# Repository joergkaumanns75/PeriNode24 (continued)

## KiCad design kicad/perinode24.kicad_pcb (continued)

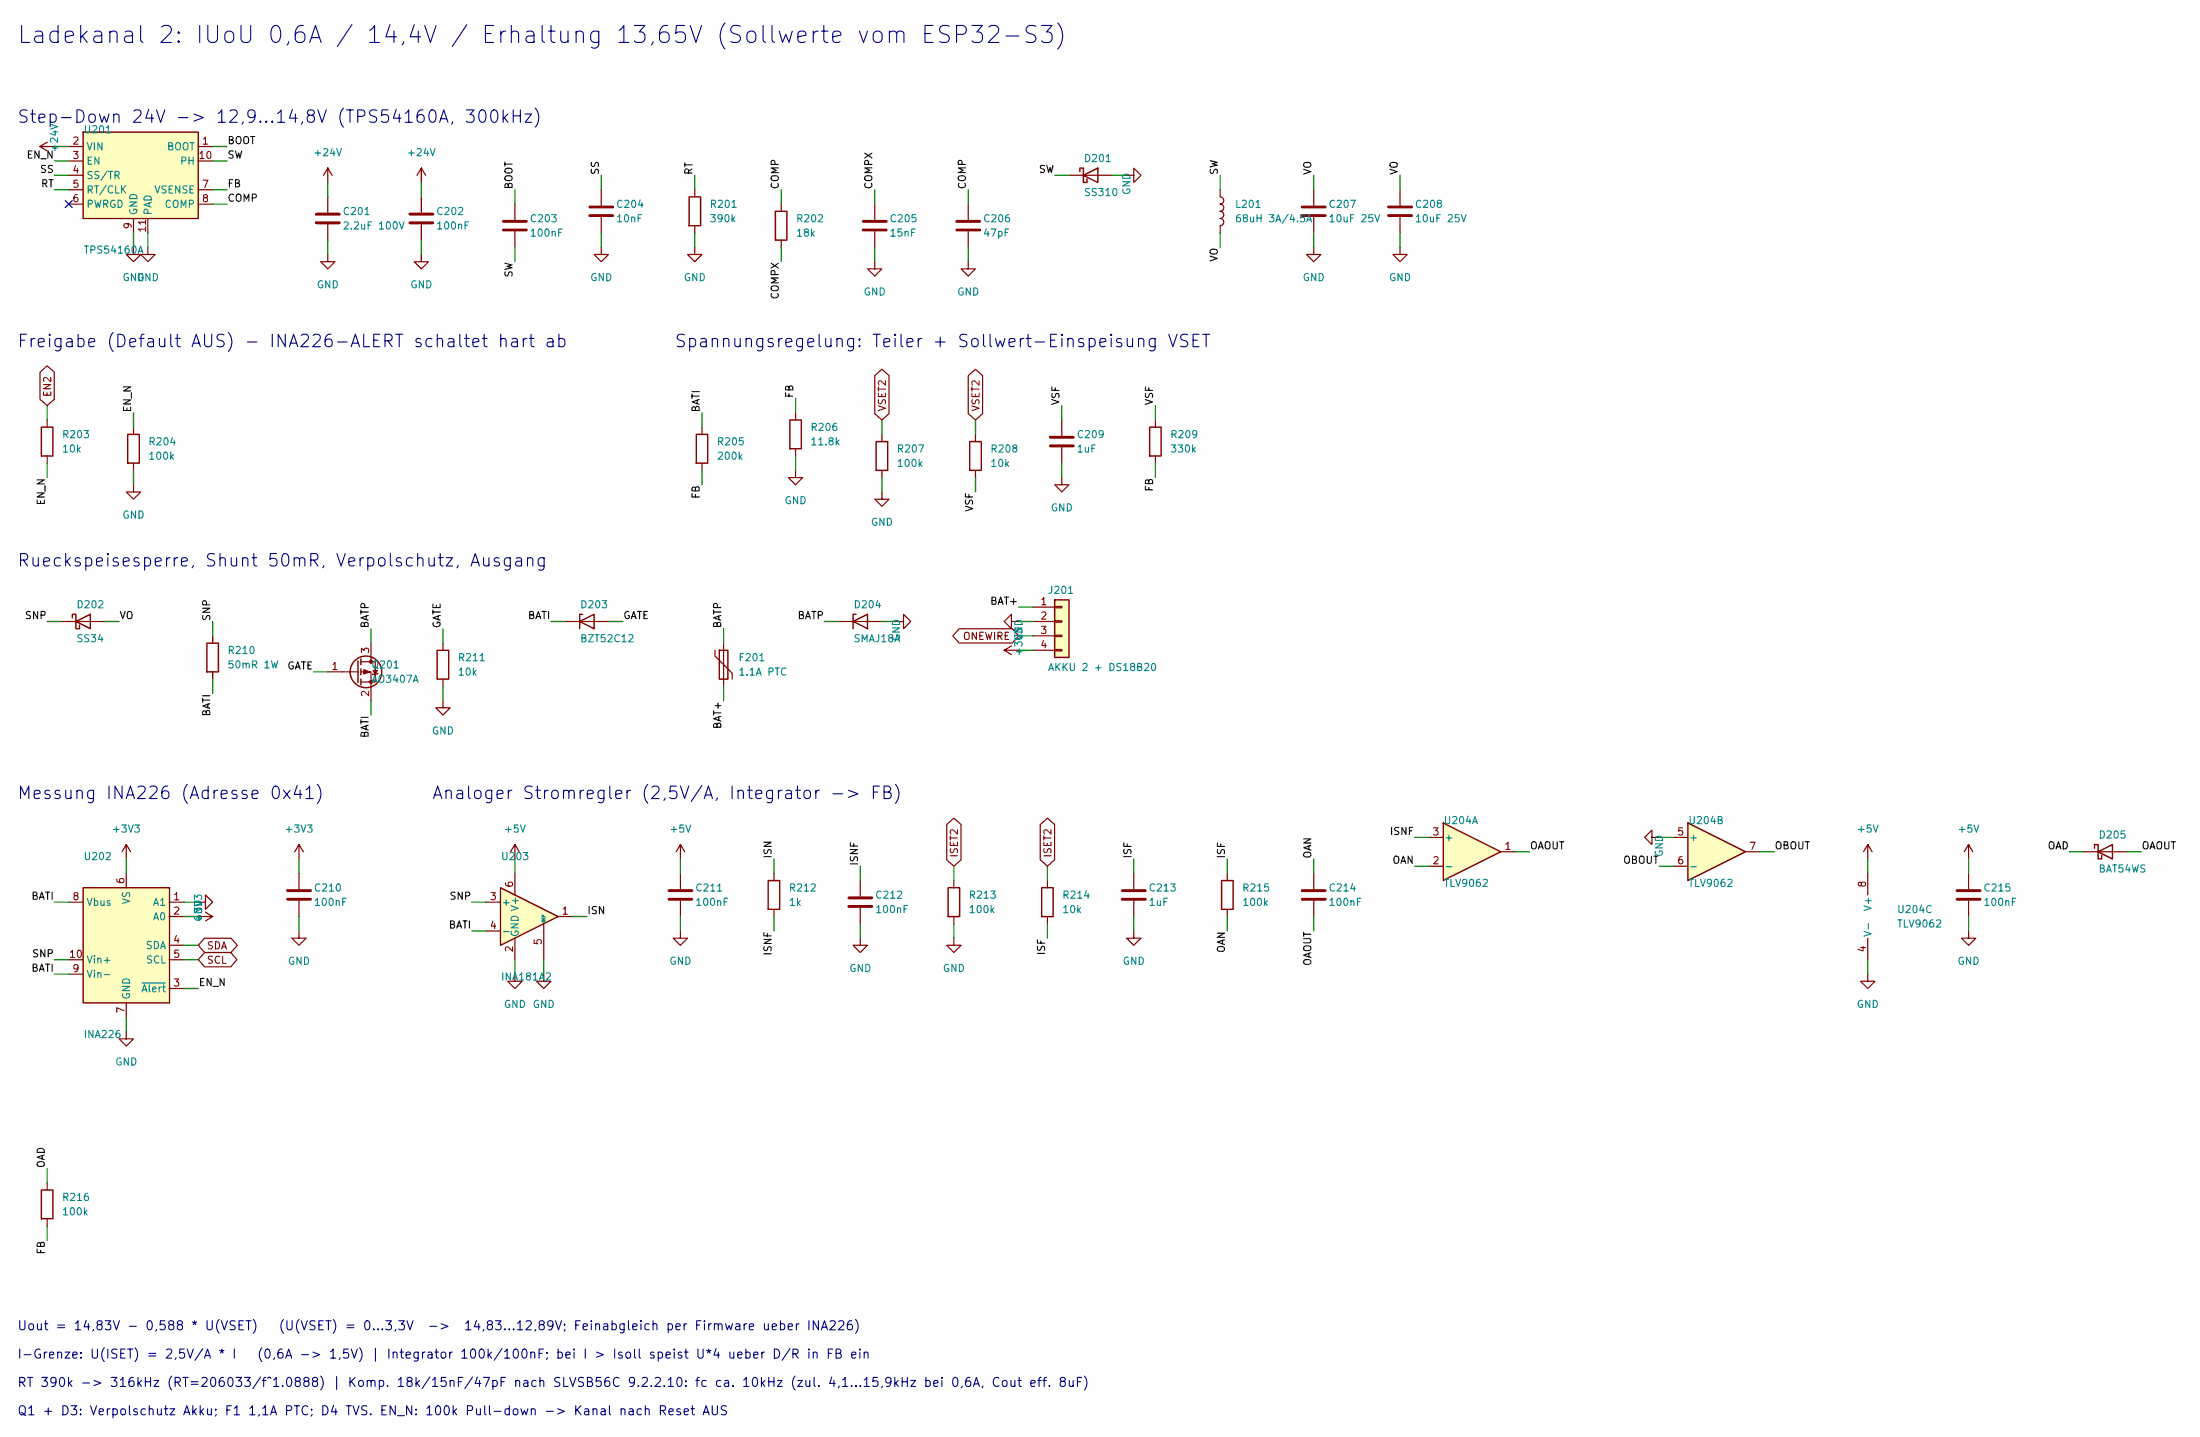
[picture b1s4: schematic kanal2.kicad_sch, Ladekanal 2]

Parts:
C201: 2.2uF 100V; C_1210_3225Metric; MPN CL32B225KCJSNNE; LCSC C55151
C202, C203, C210, C211, C212, C214, C215: 100nF; C_0603_1608Metric; MPN CC0603KRX7R9BB104; LCSC C14663
C204: 10nF; C_0603_1608Metric; MPN 0603B103K500NT; LCSC C57112
C205: 15nF; C_0603_1608Metric; MPN 0603B153K500CT; LCSC C296018
C206: 47pF; C_0603_1608Metric; MPN 0603CG470J500NT; LCSC C1671
C207, C208: 10uF 25V; C_0805_2012Metric; MPN CL21A106KAYNNNE; LCSC C15850
C209, C213: 1uF; C_0603_1608Metric; MPN CL10A105KB8NNNC; LCSC C15849
D201: SS310; D_SMA; MPN SS310; LCSC C15874
D202: SS34; D_SMA; MPN SS34; LCSC C8678
D203: BZT52C12; D_SOD-123; MPN BZT52C12; LCSC C2891780
D204: SMAJ18A; D_SMA; MPN SMAJ18A; LCSC C148219
D205: BAT54WS; D_SOD-323; MPN BAT54WS; LCSC C3040452
F201: 1.1A PTC; Fuse_1812_4532Metric; MPN 1812L110/16DR; LCSC C142746
J201: AKKU 2 + DS18B20; JST_PH_S4B-PH-SM4-TB_1x04-1MP_P2.00mm_Horizontal; MPN S4B-PH-SM4-TB(LF)(SN); LCSC C265102
L201: 68uH 3A/4.5A; L_TaiTech_TMPC1265_13.5x12.5mm; MPN FXL1360-680-M; LCSC C526032
Q201: AO3407A; SOT-23; MPN AO3407A; LCSC C15155
R201: 390k; R_0603_1608Metric; MPN 0603WAF3903T5E; LCSC C23150
R202: 18k; R_0603_1608Metric; MPN 0603WAF1802T5E; LCSC C25810
R203, R208, R211, R214: 10k; R_0603_1608Metric; MPN 0603WAF1002T5E; LCSC C25804
R204, R207, R213, R215, R216: 100k; R_0603_1608Metric; MPN 0603WAF1003T5E; LCSC C25803
R205: 200k; R_0603_1608Metric; MPN 0603WAF2003T5E; LCSC C25811
R206: 11.8k; R_0603_1608Metric; MPN RMC060311.8K1%N; LCSC C325665
R209: 330k; R_0603_1608Metric; MPN 0603WAF3303T5E; LCSC C23137
R210: 50mR 1W; R_1206_3216Metric; MPN RLM12FTCMR050; LCSC C912768
R212: 1k; R_0603_1608Metric; MPN 0603WAF1001T5E; LCSC C21190
U201: TPS54160A; MSOP-10-1EP_3x3mm_P0.5mm_EP1.68x1.88mm_ThermalVias; MPN TPS54160ADGQR; LCSC C390949
U202: INA226; VSSOP-10_3x3mm_P0.5mm; MPN INA226AIDGSR; LCSC C49851
U203: INA181A2; SOT-23-6; MPN INA181A2IDBVR; LCSC C2058784
U204: TLV9062; SOIC-8_3.9x4.9mm_P1.27mm; MPN TLV9062IDR; LCSC C398355

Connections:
+3V3: C210.1, J201.4, U202.2 (A0), U202.6 (VS); also elsewhere on the board
+5V: C211.1, C215.1, U203.6 (V+), U204.8 (V+); also elsewhere on the board
+24V: C201.1, C202.1, U201.2 (VIN); also elsewhere on the board
/Ladekanal 2/BAT+: F201.2, J201.1
/Ladekanal 2/BATI: D203.1 (K), Q201.2 (S), R205.1, R210.2, U202.8 (Vbus), U202.9 (Vin-), U203.4 (-)
/Ladekanal 2/BATP: D204.1 (K), F201.1, Q201.3 (D)
/Ladekanal 2/BOOT: C203.1, U201.1 (BOOT)
/Ladekanal 2/COMP: C206.1, R202.1, U201.8 (COMP)
/Ladekanal 2/COMPX: C205.1, R202.2
/Ladekanal 2/EN_N: R203.2, R204.1, U201.3 (EN), U202.3 (~Alert)
/Ladekanal 2/FB: R205.2, R206.1, R209.2, R216.2, U201.7 (VSENSE)
/Ladekanal 2/GATE: D203.2 (A), Q201.1 (G), R211.1
/Ladekanal 2/ISF: C213.1, R214.2, R215.1
/Ladekanal 2/ISN: R212.1, U203.1
/Ladekanal 2/ISNF: C212.1, R212.2, U204.3 (+)
/Ladekanal 2/OAD: D205.1 (K), R216.1
/Ladekanal 2/OAN: C214.1, R215.2, U204.2 (-)
/Ladekanal 2/OAOUT: C214.2, D205.2 (A), U204.1
/Ladekanal 2/OBOUT: U204.6 (-), U204.7
/Ladekanal 2/RT: R201.1, U201.5 (RT/CLK)
/Ladekanal 2/SNP: D202.1 (K), R210.1, U202.10 (Vin+), U203.3 (+)
/Ladekanal 2/SS: C204.1, U201.4 (SS/TR)
/Ladekanal 2/SW: C203.2, D201.1 (K), L201.1, U201.10 (PH)
/Ladekanal 2/VO: C207.1, C208.1, D202.2 (A), L201.2
/Ladekanal 2/VSF: C209.1, R208.2, R209.1
EN2: R203.1; also elsewhere on the board
GND: C201.2, C202.2, C204.2, C205.2, C206.2, C207.2, C208.2, C209.2, C210.2, C211.2, C212.2, C213.2, C215.2, D201.2 (A), D204.2 (A), J201.2, R201.2, R204.2, R206.2, R207.2, R211.2, R213.2, U201.9 (GND), U201.11 (PAD), U202.1 (A1), U202.7 (GND), U203.2 (GND), U203.5 (REF), U204.4 (V-), U204.5 (+); also elsewhere on the board
ISET2: R213.1, R214.1; also elsewhere on the board
ONEWIRE: J201.3; also elsewhere on the board
SCL: U202.5 (SCL); also elsewhere on the board
SDA: U202.4 (SDA); also elsewhere on the board
VSET2: R207.1, R208.1; also elsewhere on the board

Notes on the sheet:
I-Grenze: U(ISET) = 2,5V/A * I (0,6A -> 1,5V) | Integrator 100k/100nF; bei I > Isoll speist U*4 ueber D/R in FB ein
Step-Down 24V -> 12,9...14,8V (TPS54160A, 300kHz)
Uout = 14,83V - 0,588 * U(VSET) (U(VSET) = 0...3,3V -> 14,83...12,89V; Feinabgleich per Firmware ueber INA226)
Analoger Stromregler (2,5V/A, Integrator -> FB)
Freigabe (Default AUS) - INA226-ALERT schaltet hart ab
Rueckspeisesperre, Shunt 50mR, Verpolschutz, Ausgang
Spannungsregelung: Teiler + Sollwert-Einspeisung VSET
Q1 + D3: Verpolschutz Akku; F1 1,1A PTC; D4 TVS. EN_N: 100k Pull-down -> Kanal nach Reset AUS
Messung INA226 (Adresse 0x41)
RT 390k -> 316kHz (RT=206033/f^1.0888) | Komp. 18k/15nF/47pF nach SLVSB56C 9.2.2.10: fc ca. 10kHz (zul. 4,1...15,9kHz bei 0,6A, Cout eff. 8uF)
Ladekanal 2: IUoU 0,6A / 14,4V / Erhaltung 13,65V (Sollwerte vom ESP32-S3)

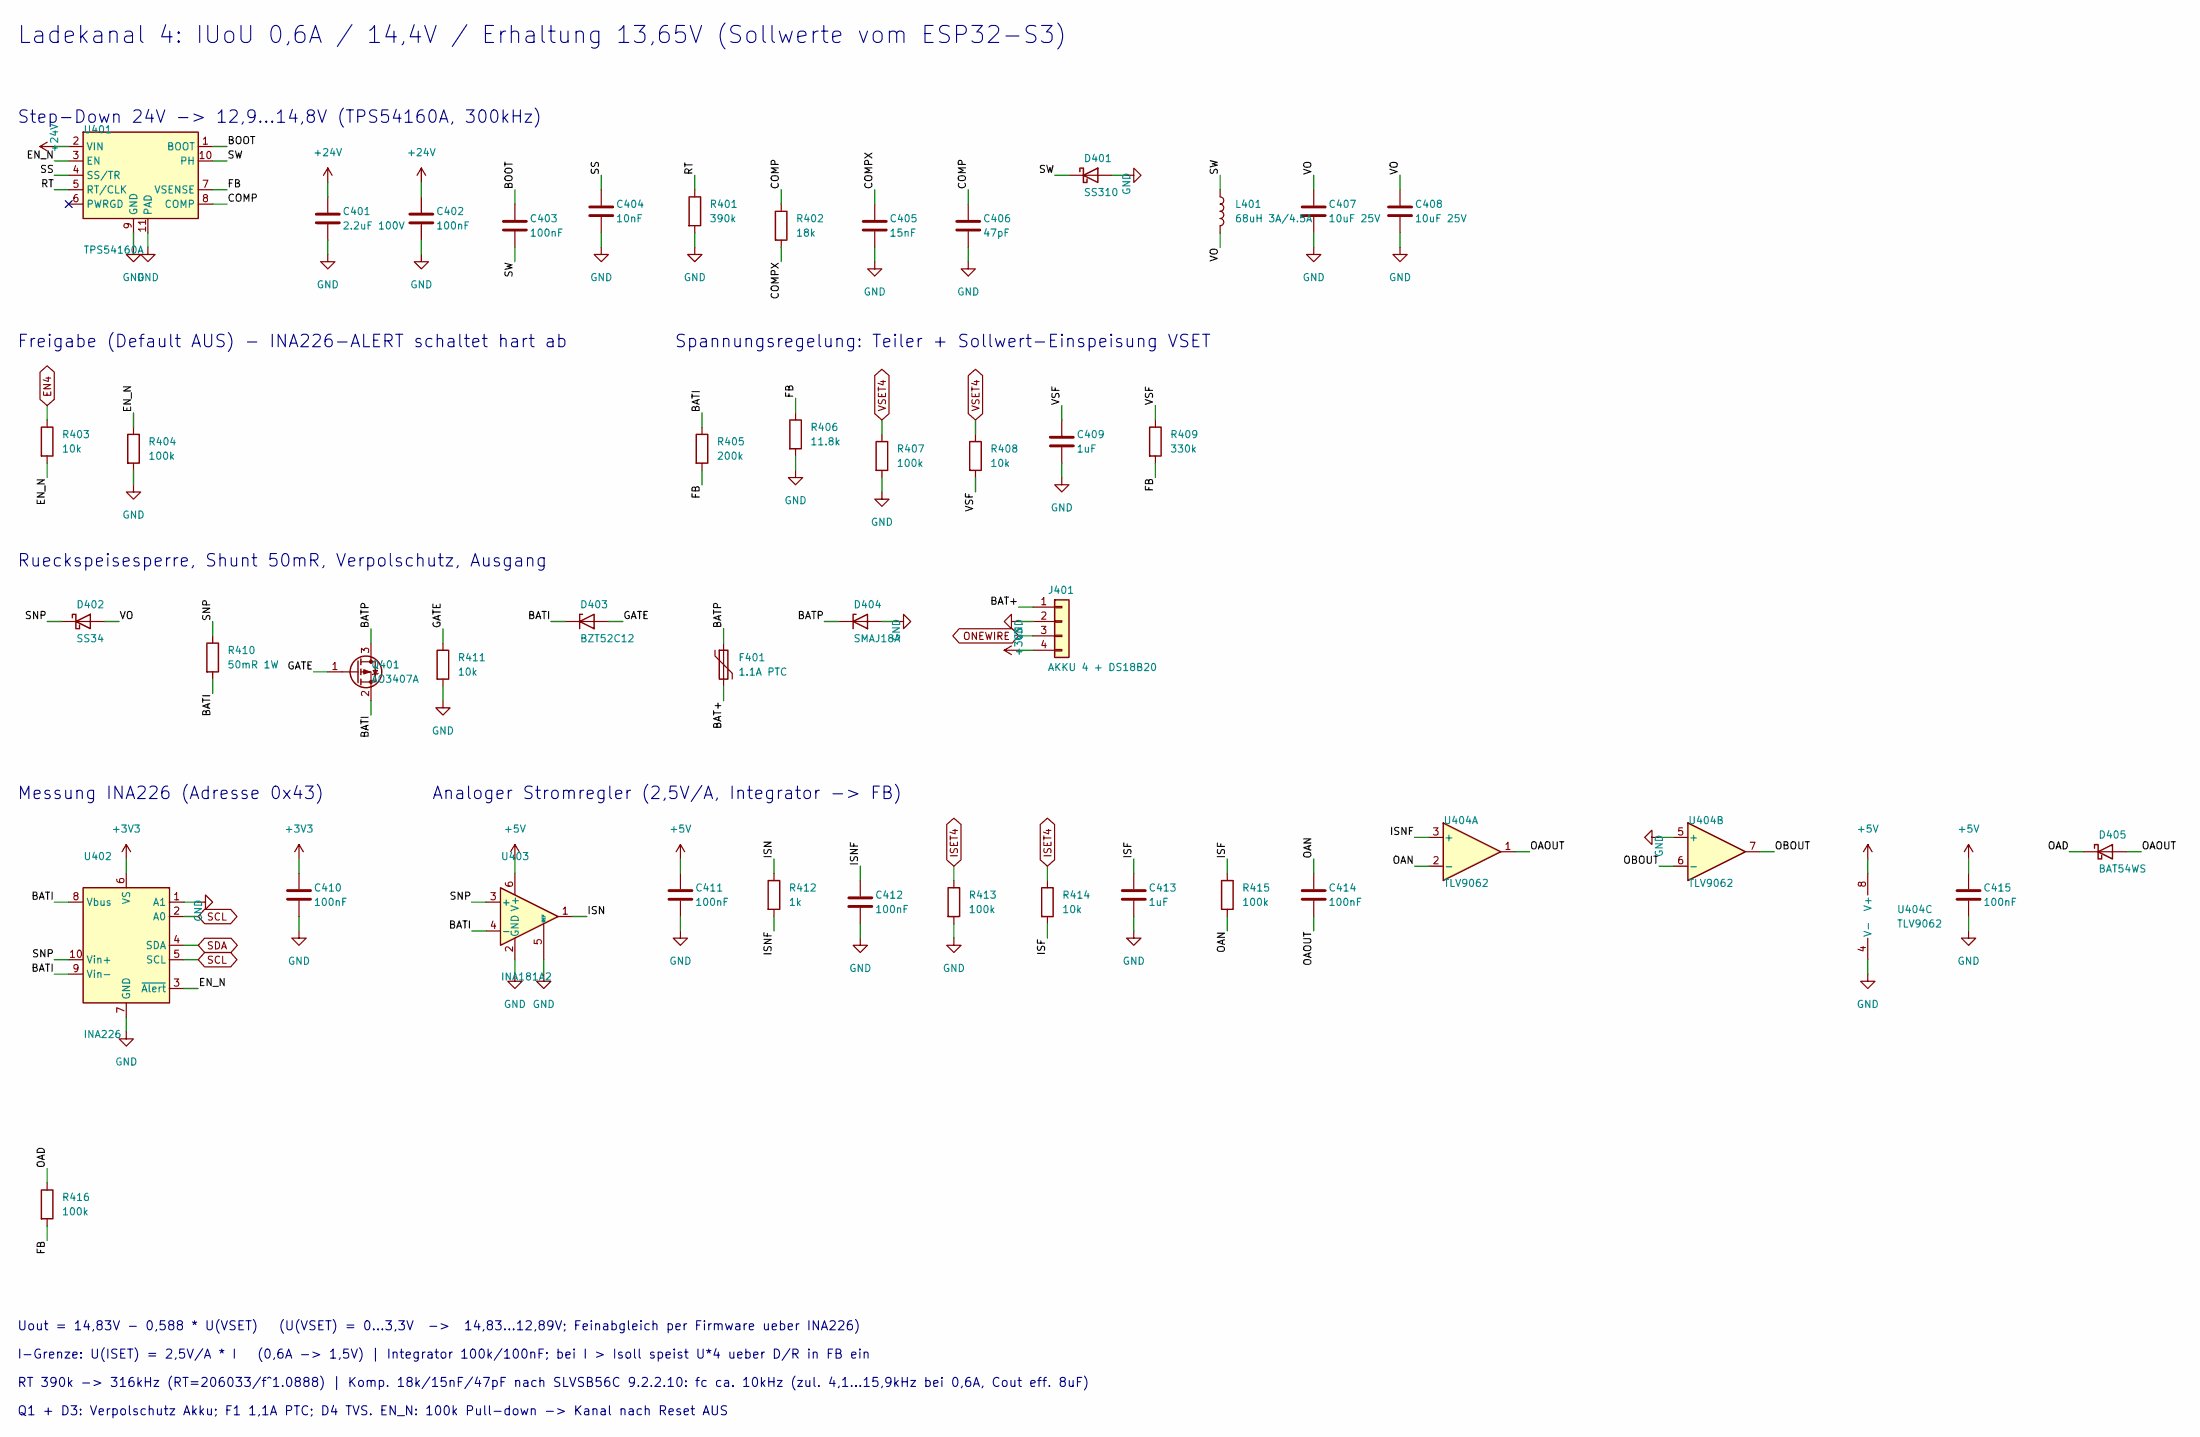
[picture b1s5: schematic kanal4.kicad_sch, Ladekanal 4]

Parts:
C401: 2.2uF 100V; C_1210_3225Metric; MPN CL32B225KCJSNNE; LCSC C55151
C402, C403, C410, C411, C412, C414, C415: 100nF; C_0603_1608Metric; MPN CC0603KRX7R9BB104; LCSC C14663
C404: 10nF; C_0603_1608Metric; MPN 0603B103K500NT; LCSC C57112
C405: 15nF; C_0603_1608Metric; MPN 0603B153K500CT; LCSC C296018
C406: 47pF; C_0603_1608Metric; MPN 0603CG470J500NT; LCSC C1671
C407, C408: 10uF 25V; C_0805_2012Metric; MPN CL21A106KAYNNNE; LCSC C15850
C409, C413: 1uF; C_0603_1608Metric; MPN CL10A105KB8NNNC; LCSC C15849
D401: SS310; D_SMA; MPN SS310; LCSC C15874
D402: SS34; D_SMA; MPN SS34; LCSC C8678
D403: BZT52C12; D_SOD-123; MPN BZT52C12; LCSC C2891780
D404: SMAJ18A; D_SMA; MPN SMAJ18A; LCSC C148219
D405: BAT54WS; D_SOD-323; MPN BAT54WS; LCSC C3040452
F401: 1.1A PTC; Fuse_1812_4532Metric; MPN 1812L110/16DR; LCSC C142746
J401: AKKU 4 + DS18B20; JST_PH_S4B-PH-SM4-TB_1x04-1MP_P2.00mm_Horizontal; MPN S4B-PH-SM4-TB(LF)(SN); LCSC C265102
L401: 68uH 3A/4.5A; L_TaiTech_TMPC1265_13.5x12.5mm; MPN FXL1360-680-M; LCSC C526032
Q401: AO3407A; SOT-23; MPN AO3407A; LCSC C15155
R401: 390k; R_0603_1608Metric; MPN 0603WAF3903T5E; LCSC C23150
R402: 18k; R_0603_1608Metric; MPN 0603WAF1802T5E; LCSC C25810
R403, R408, R411, R414: 10k; R_0603_1608Metric; MPN 0603WAF1002T5E; LCSC C25804
R404, R407, R413, R415, R416: 100k; R_0603_1608Metric; MPN 0603WAF1003T5E; LCSC C25803
R405: 200k; R_0603_1608Metric; MPN 0603WAF2003T5E; LCSC C25811
R406: 11.8k; R_0603_1608Metric; MPN RMC060311.8K1%N; LCSC C325665
R409: 330k; R_0603_1608Metric; MPN 0603WAF3303T5E; LCSC C23137
R410: 50mR 1W; R_1206_3216Metric; MPN RLM12FTCMR050; LCSC C912768
R412: 1k; R_0603_1608Metric; MPN 0603WAF1001T5E; LCSC C21190
U401: TPS54160A; MSOP-10-1EP_3x3mm_P0.5mm_EP1.68x1.88mm_ThermalVias; MPN TPS54160ADGQR; LCSC C390949
U402: INA226; VSSOP-10_3x3mm_P0.5mm; MPN INA226AIDGSR; LCSC C49851
U403: INA181A2; SOT-23-6; MPN INA181A2IDBVR; LCSC C2058784
U404: TLV9062; SOIC-8_3.9x4.9mm_P1.27mm; MPN TLV9062IDR; LCSC C398355

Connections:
+3V3: C410.1, J401.4, U402.6 (VS); also elsewhere on the board
+5V: C411.1, C415.1, U403.6 (V+), U404.8 (V+); also elsewhere on the board
+24V: C401.1, C402.1, U401.2 (VIN); also elsewhere on the board
/Ladekanal 4/BAT+: F401.2, J401.1
/Ladekanal 4/BATI: D403.1 (K), Q401.2 (S), R405.1, R410.2, U402.8 (Vbus), U402.9 (Vin-), U403.4 (-)
/Ladekanal 4/BATP: D404.1 (K), F401.1, Q401.3 (D)
/Ladekanal 4/BOOT: C403.1, U401.1 (BOOT)
/Ladekanal 4/COMP: C406.1, R402.1, U401.8 (COMP)
/Ladekanal 4/COMPX: C405.1, R402.2
/Ladekanal 4/EN_N: R403.2, R404.1, U401.3 (EN), U402.3 (~Alert)
/Ladekanal 4/FB: R405.2, R406.1, R409.2, R416.2, U401.7 (VSENSE)
/Ladekanal 4/GATE: D403.2 (A), Q401.1 (G), R411.1
/Ladekanal 4/ISF: C413.1, R414.2, R415.1
/Ladekanal 4/ISN: R412.1, U403.1
/Ladekanal 4/ISNF: C412.1, R412.2, U404.3 (+)
/Ladekanal 4/OAD: D405.1 (K), R416.1
/Ladekanal 4/OAN: C414.1, R415.2, U404.2 (-)
/Ladekanal 4/OAOUT: C414.2, D405.2 (A), U404.1
/Ladekanal 4/OBOUT: U404.6 (-), U404.7
/Ladekanal 4/RT: R401.1, U401.5 (RT/CLK)
/Ladekanal 4/SNP: D402.1 (K), R410.1, U402.10 (Vin+), U403.3 (+)
/Ladekanal 4/SS: C404.1, U401.4 (SS/TR)
/Ladekanal 4/SW: C403.2, D401.1 (K), L401.1, U401.10 (PH)
/Ladekanal 4/VO: C407.1, C408.1, D402.2 (A), L401.2
/Ladekanal 4/VSF: C409.1, R408.2, R409.1
EN4: R403.1; also elsewhere on the board
GND: C401.2, C402.2, C404.2, C405.2, C406.2, C407.2, C408.2, C409.2, C410.2, C411.2, C412.2, C413.2, C415.2, D401.2 (A), D404.2 (A), J401.2, R401.2, R404.2, R406.2, R407.2, R411.2, R413.2, U401.9 (GND), U401.11 (PAD), U402.1 (A1), U402.7 (GND), U403.2 (GND), U403.5 (REF), U404.4 (V-), U404.5 (+); also elsewhere on the board
ISET4: R413.1, R414.1; also elsewhere on the board
ONEWIRE: J401.3; also elsewhere on the board
SCL: U402.2 (A0), U402.5 (SCL); also elsewhere on the board
SDA: U402.4 (SDA); also elsewhere on the board
VSET4: R407.1, R408.1; also elsewhere on the board

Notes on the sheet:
Ladekanal 4: IUoU 0,6A / 14,4V / Erhaltung 13,65V (Sollwerte vom ESP32-S3)
Step-Down 24V -> 12,9...14,8V (TPS54160A, 300kHz)
Freigabe (Default AUS) - INA226-ALERT schaltet hart ab
Spannungsregelung: Teiler + Sollwert-Einspeisung VSET
Rueckspeisesperre, Shunt 50mR, Verpolschutz, Ausgang
Messung INA226 (Adresse 0x43)
Analoger Stromregler (2,5V/A, Integrator -> FB)
Uout = 14,83V - 0,588 * U(VSET) (U(VSET) = 0...3,3V -> 14,83...12,89V; Feinabgleich per Firmware ueber INA226)
I-Grenze: U(ISET) = 2,5V/A * I (0,6A -> 1,5V) | Integrator 100k/100nF; bei I > Isoll speist U*4 ueber D/R in FB ein
RT 390k -> 316kHz (RT=206033/f^1.0888) | Komp. 18k/15nF/47pF nach SLVSB56C 9.2.2.10: fc ca. 10kHz (zul. 4,1...15,9kHz bei 0,6A, Cout eff. 8uF)
Q1 + D3: Verpolschutz Akku; F1 1,1A PTC; D4 TVS. EN_N: 100k Pull-down -> Kanal nach Reset AUS

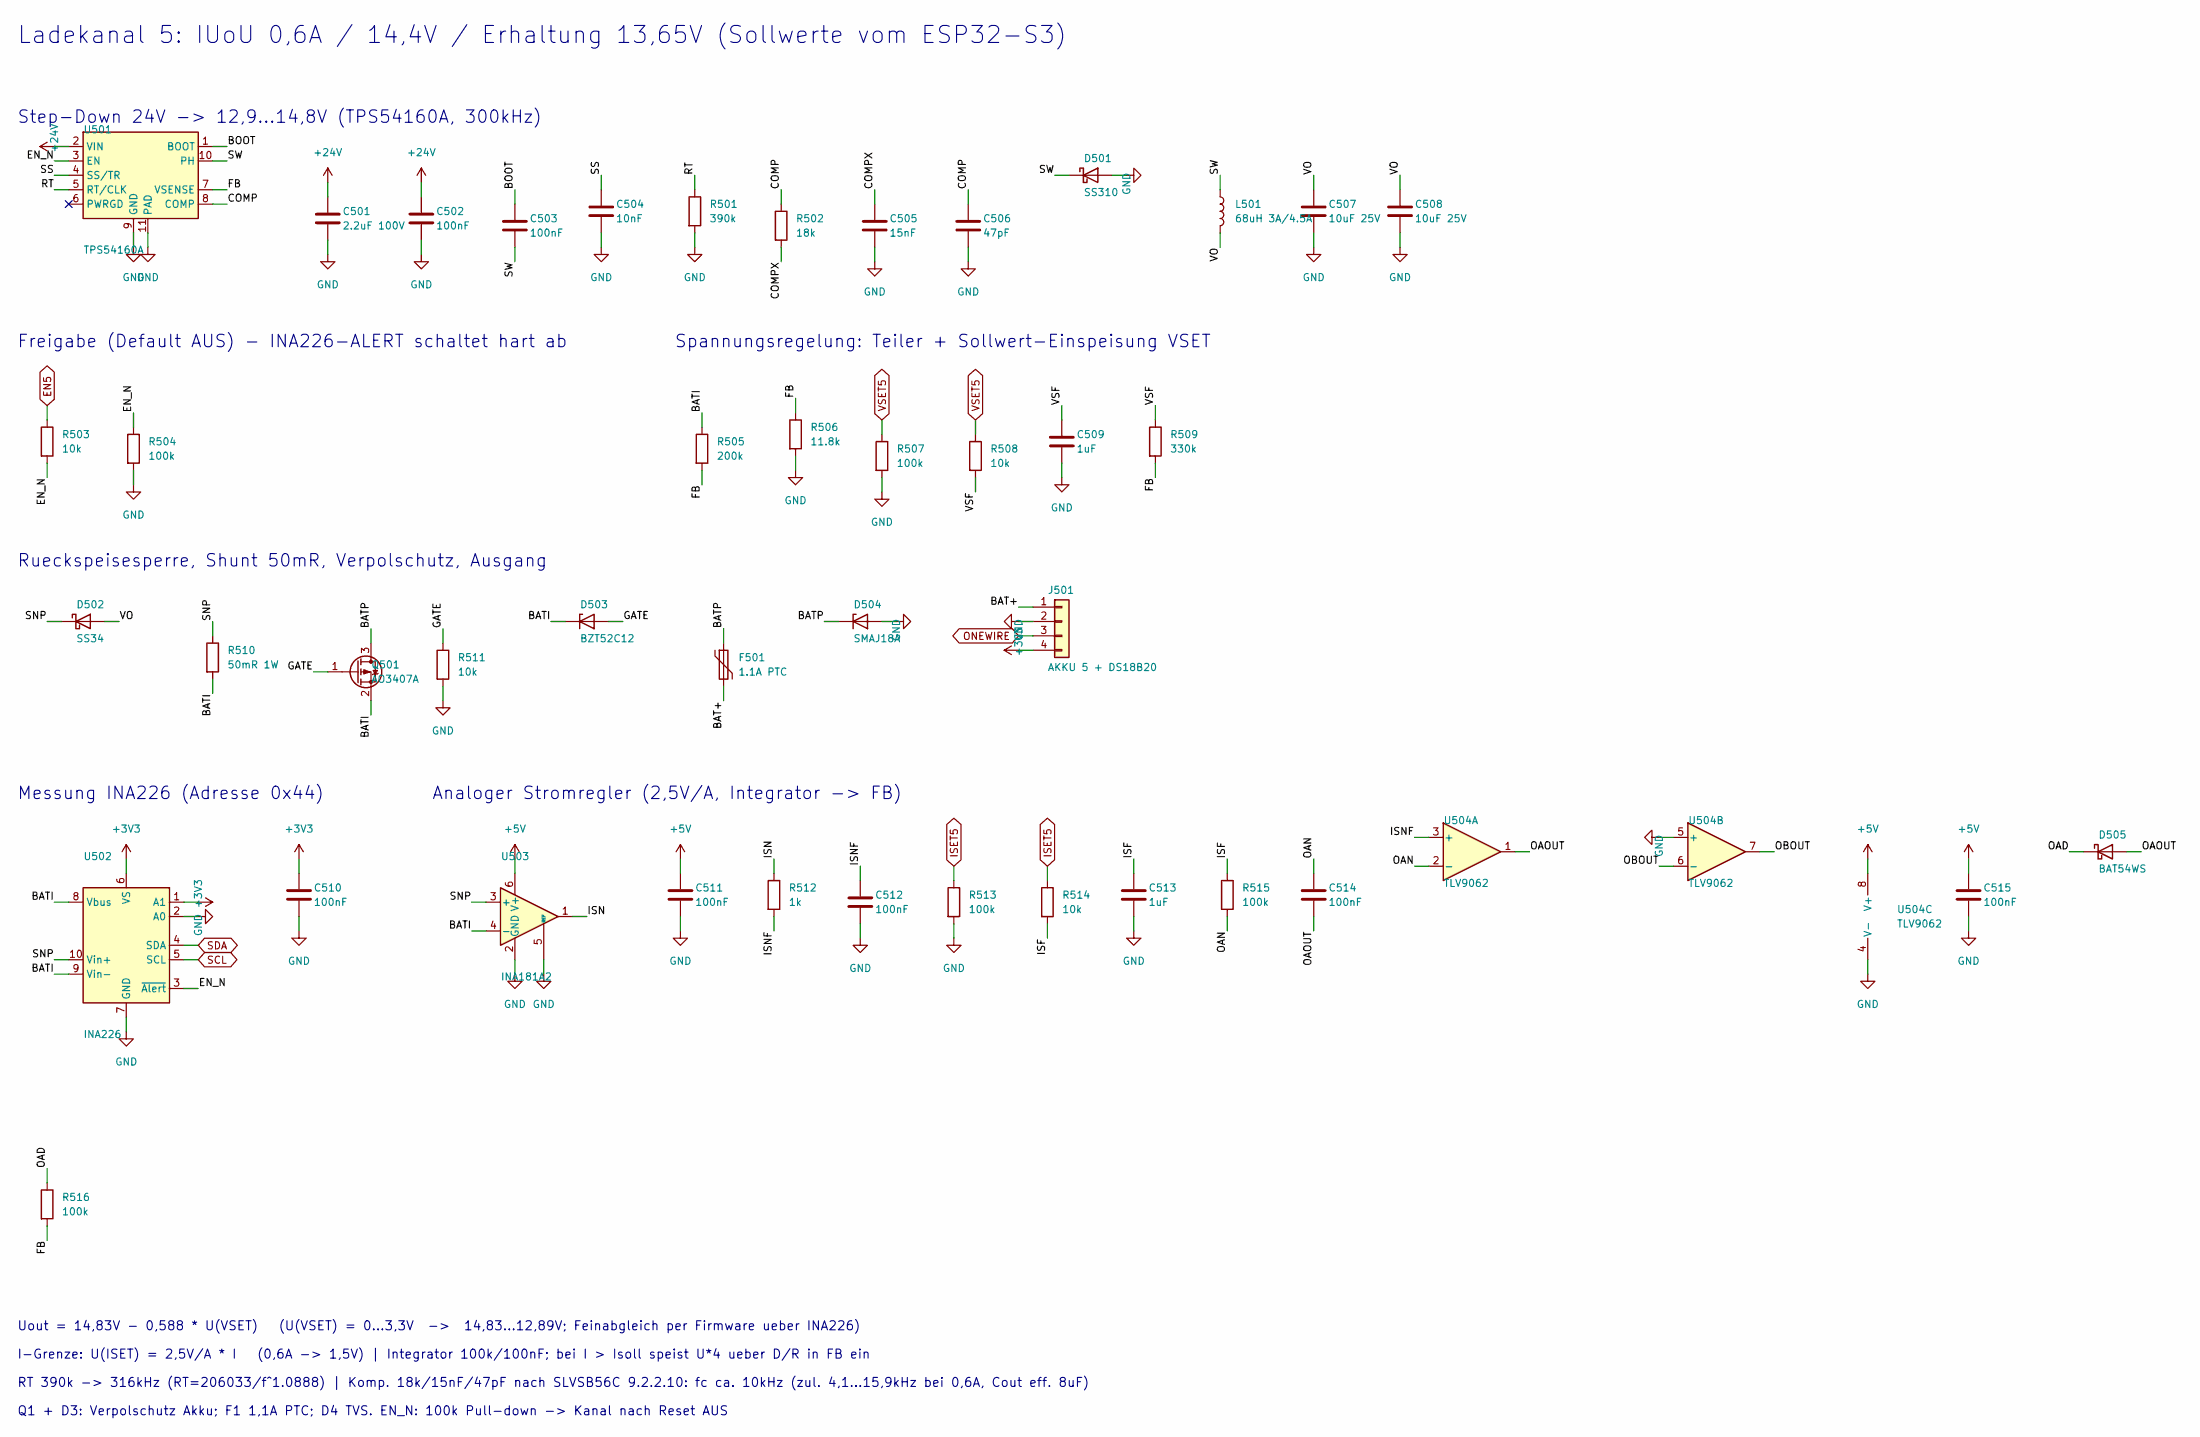
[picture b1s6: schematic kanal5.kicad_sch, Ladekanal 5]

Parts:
C501: 2.2uF 100V; C_1210_3225Metric; MPN CL32B225KCJSNNE; LCSC C55151
C502, C503, C510, C511, C512, C514, C515: 100nF; C_0603_1608Metric; MPN CC0603KRX7R9BB104; LCSC C14663
C504: 10nF; C_0603_1608Metric; MPN 0603B103K500NT; LCSC C57112
C505: 15nF; C_0603_1608Metric; MPN 0603B153K500CT; LCSC C296018
C506: 47pF; C_0603_1608Metric; MPN 0603CG470J500NT; LCSC C1671
C507, C508: 10uF 25V; C_0805_2012Metric; MPN CL21A106KAYNNNE; LCSC C15850
C509, C513: 1uF; C_0603_1608Metric; MPN CL10A105KB8NNNC; LCSC C15849
D501: SS310; D_SMA; MPN SS310; LCSC C15874
D502: SS34; D_SMA; MPN SS34; LCSC C8678
D503: BZT52C12; D_SOD-123; MPN BZT52C12; LCSC C2891780
D504: SMAJ18A; D_SMA; MPN SMAJ18A; LCSC C148219
D505: BAT54WS; D_SOD-323; MPN BAT54WS; LCSC C3040452
F501: 1.1A PTC; Fuse_1812_4532Metric; MPN 1812L110/16DR; LCSC C142746
J501: AKKU 5 + DS18B20; JST_PH_S4B-PH-SM4-TB_1x04-1MP_P2.00mm_Horizontal; MPN S4B-PH-SM4-TB(LF)(SN); LCSC C265102
L501: 68uH 3A/4.5A; L_TaiTech_TMPC1265_13.5x12.5mm; MPN FXL1360-680-M; LCSC C526032
Q501: AO3407A; SOT-23; MPN AO3407A; LCSC C15155
R501: 390k; R_0603_1608Metric; MPN 0603WAF3903T5E; LCSC C23150
R502: 18k; R_0603_1608Metric; MPN 0603WAF1802T5E; LCSC C25810
R503, R508, R511, R514: 10k; R_0603_1608Metric; MPN 0603WAF1002T5E; LCSC C25804
R504, R507, R513, R515, R516: 100k; R_0603_1608Metric; MPN 0603WAF1003T5E; LCSC C25803
R505: 200k; R_0603_1608Metric; MPN 0603WAF2003T5E; LCSC C25811
R506: 11.8k; R_0603_1608Metric; MPN RMC060311.8K1%N; LCSC C325665
R509: 330k; R_0603_1608Metric; MPN 0603WAF3303T5E; LCSC C23137
R510: 50mR 1W; R_1206_3216Metric; MPN RLM12FTCMR050; LCSC C912768
R512: 1k; R_0603_1608Metric; MPN 0603WAF1001T5E; LCSC C21190
U501: TPS54160A; MSOP-10-1EP_3x3mm_P0.5mm_EP1.68x1.88mm_ThermalVias; MPN TPS54160ADGQR; LCSC C390949
U502: INA226; VSSOP-10_3x3mm_P0.5mm; MPN INA226AIDGSR; LCSC C49851
U503: INA181A2; SOT-23-6; MPN INA181A2IDBVR; LCSC C2058784
U504: TLV9062; SOIC-8_3.9x4.9mm_P1.27mm; MPN TLV9062IDR; LCSC C398355

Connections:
+3V3: C510.1, J501.4, U502.1 (A1), U502.6 (VS); also elsewhere on the board
+5V: C511.1, C515.1, U503.6 (V+), U504.8 (V+); also elsewhere on the board
+24V: C501.1, C502.1, U501.2 (VIN); also elsewhere on the board
/Ladekanal 5/BAT+: F501.2, J501.1
/Ladekanal 5/BATI: D503.1 (K), Q501.2 (S), R505.1, R510.2, U502.8 (Vbus), U502.9 (Vin-), U503.4 (-)
/Ladekanal 5/BATP: D504.1 (K), F501.1, Q501.3 (D)
/Ladekanal 5/BOOT: C503.1, U501.1 (BOOT)
/Ladekanal 5/COMP: C506.1, R502.1, U501.8 (COMP)
/Ladekanal 5/COMPX: C505.1, R502.2
/Ladekanal 5/EN_N: R503.2, R504.1, U501.3 (EN), U502.3 (~Alert)
/Ladekanal 5/FB: R505.2, R506.1, R509.2, R516.2, U501.7 (VSENSE)
/Ladekanal 5/GATE: D503.2 (A), Q501.1 (G), R511.1
/Ladekanal 5/ISF: C513.1, R514.2, R515.1
/Ladekanal 5/ISN: R512.1, U503.1
/Ladekanal 5/ISNF: C512.1, R512.2, U504.3 (+)
/Ladekanal 5/OAD: D505.1 (K), R516.1
/Ladekanal 5/OAN: C514.1, R515.2, U504.2 (-)
/Ladekanal 5/OAOUT: C514.2, D505.2 (A), U504.1
/Ladekanal 5/OBOUT: U504.6 (-), U504.7
/Ladekanal 5/RT: R501.1, U501.5 (RT/CLK)
/Ladekanal 5/SNP: D502.1 (K), R510.1, U502.10 (Vin+), U503.3 (+)
/Ladekanal 5/SS: C504.1, U501.4 (SS/TR)
/Ladekanal 5/SW: C503.2, D501.1 (K), L501.1, U501.10 (PH)
/Ladekanal 5/VO: C507.1, C508.1, D502.2 (A), L501.2
/Ladekanal 5/VSF: C509.1, R508.2, R509.1
EN5: R503.1; also elsewhere on the board
GND: C501.2, C502.2, C504.2, C505.2, C506.2, C507.2, C508.2, C509.2, C510.2, C511.2, C512.2, C513.2, C515.2, D501.2 (A), D504.2 (A), J501.2, R501.2, R504.2, R506.2, R507.2, R511.2, R513.2, U501.9 (GND), U501.11 (PAD), U502.2 (A0), U502.7 (GND), U503.2 (GND), U503.5 (REF), U504.4 (V-), U504.5 (+); also elsewhere on the board
ISET5: R513.1, R514.1; also elsewhere on the board
ONEWIRE: J501.3; also elsewhere on the board
SCL: U502.5 (SCL); also elsewhere on the board
SDA: U502.4 (SDA); also elsewhere on the board
VSET5: R507.1, R508.1; also elsewhere on the board

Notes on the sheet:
Ladekanal 5: IUoU 0,6A / 14,4V / Erhaltung 13,65V (Sollwerte vom ESP32-S3)
Step-Down 24V -> 12,9...14,8V (TPS54160A, 300kHz)
Freigabe (Default AUS) - INA226-ALERT schaltet hart ab
Spannungsregelung: Teiler + Sollwert-Einspeisung VSET
Rueckspeisesperre, Shunt 50mR, Verpolschutz, Ausgang
Messung INA226 (Adresse 0x44)
Analoger Stromregler (2,5V/A, Integrator -> FB)
Uout = 14,83V - 0,588 * U(VSET) (U(VSET) = 0...3,3V -> 14,83...12,89V; Feinabgleich per Firmware ueber INA226)
I-Grenze: U(ISET) = 2,5V/A * I (0,6A -> 1,5V) | Integrator 100k/100nF; bei I > Isoll speist U*4 ueber D/R in FB ein
RT 390k -> 316kHz (RT=206033/f^1.0888) | Komp. 18k/15nF/47pF nach SLVSB56C 9.2.2.10: fc ca. 10kHz (zul. 4,1...15,9kHz bei 0,6A, Cout eff. 8uF)
Q1 + D3: Verpolschutz Akku; F1 1,1A PTC; D4 TVS. EN_N: 100k Pull-down -> Kanal nach Reset AUS
